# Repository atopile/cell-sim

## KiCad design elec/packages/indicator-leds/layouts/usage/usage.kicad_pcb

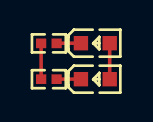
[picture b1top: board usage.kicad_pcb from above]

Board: 2 copper layers, 4 parts (0 on the bottom side), 4 nets.

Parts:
LED1, LED2: LED0603-RD
R1, R2: 4.7kΩ; R0402

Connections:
anode: LED1.2, LED2.2
cathode: LED1.1, R1.1
lv: R1.2, R2.2
red_led-cathode: LED2.1, R2.1
